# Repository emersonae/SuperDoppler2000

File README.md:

# SuperDoppler2000
BT Send Data H & T

Main loop sends Temperature and Humidity Data from AHT sensor (old sensor no pressure data)

Hm10 Bluetooth: Connect RX to PA9 and TX to PA10 

AHT20: Connect SCL to PB6 and SDA to PB7

If you want to change the message sent, or frequency make changes in the main while loop of "main.c" (core-->src-->main.c)

Rough outline of how to connect HM10 to raspberry pi here: https://docs.google.com/document/d/1dRe9r46AMOh3whqpXwOjyoZfKZXxDHSTZSgcjSjQhZo/edit?usp=sharing

using this tutorial : https://www.youtube.com/watch?v=VRqDqq9hc24

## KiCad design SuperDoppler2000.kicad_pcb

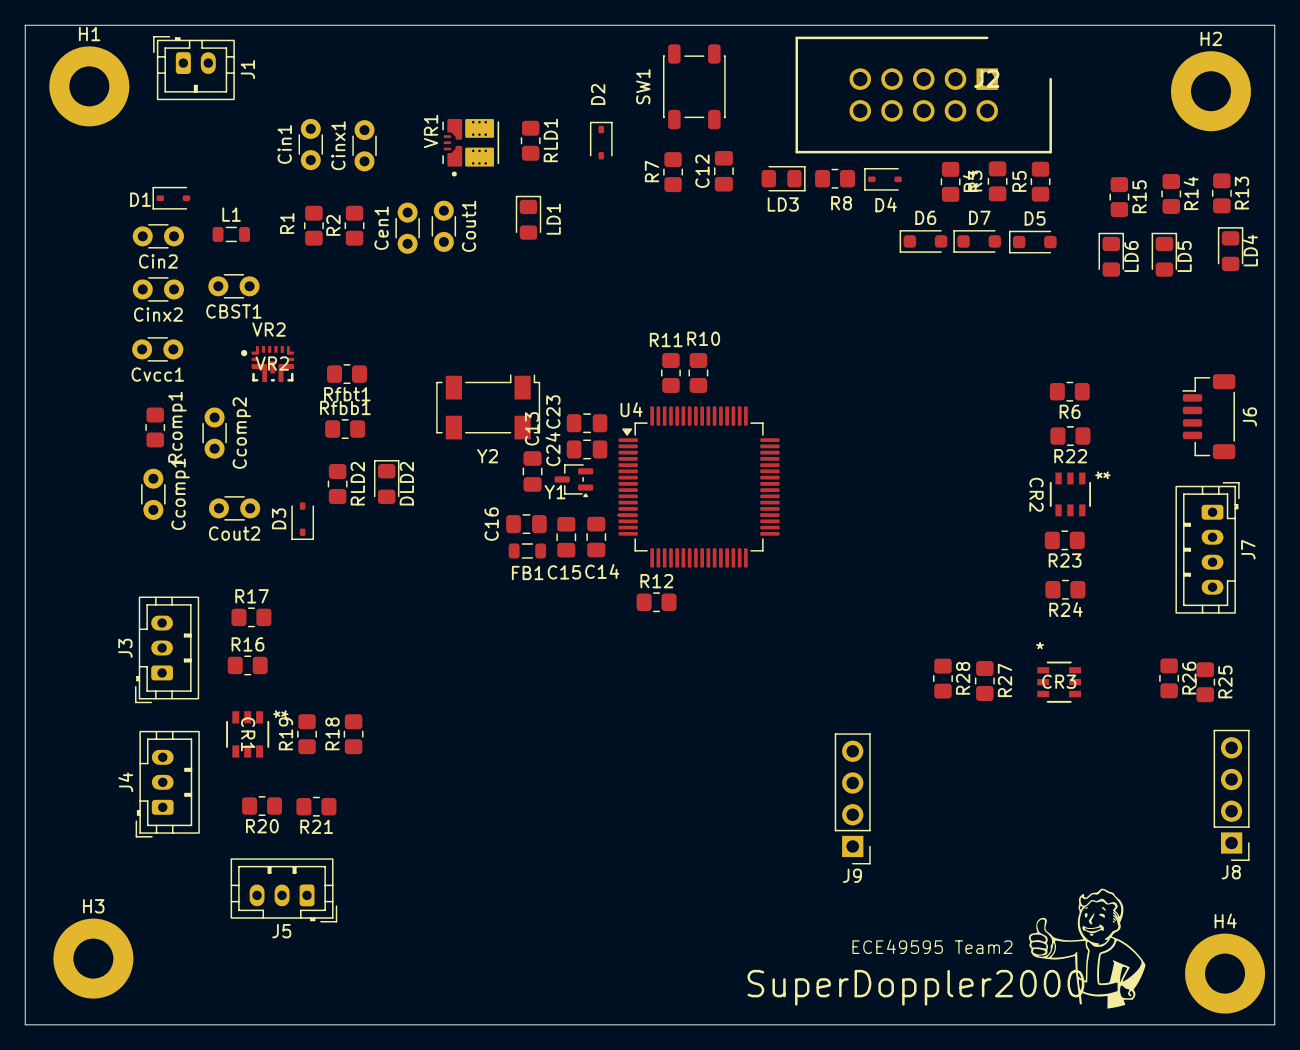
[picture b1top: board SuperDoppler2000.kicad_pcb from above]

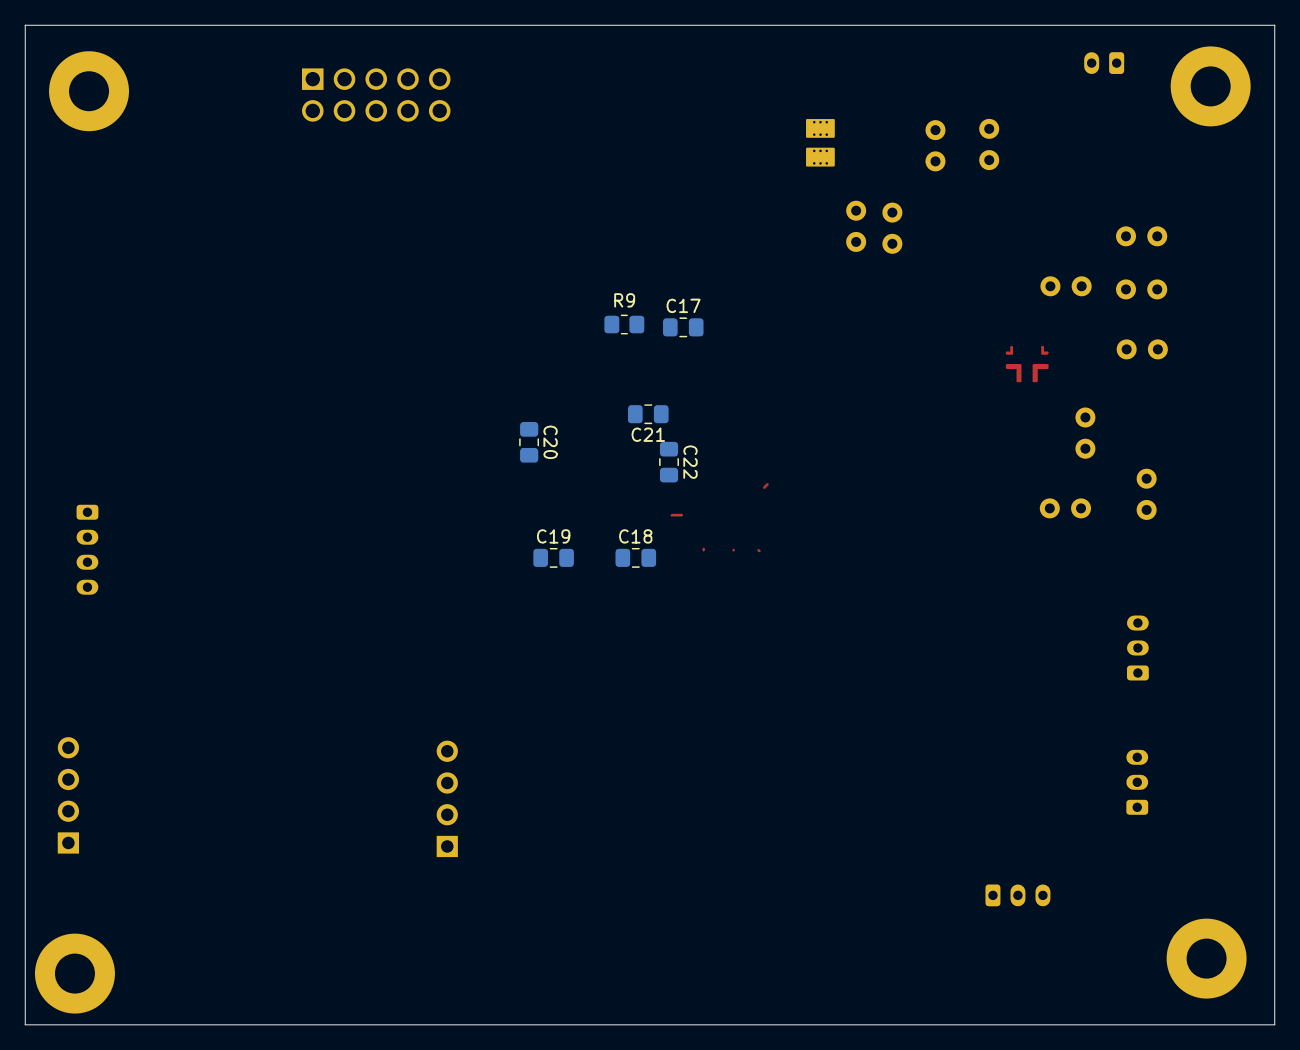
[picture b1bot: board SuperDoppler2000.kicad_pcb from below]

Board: 2 copper layers, 100.0 x 80.0 mm, 94 parts (7 on the bottom side), 58 nets.

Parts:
C12, C13: 0.1u; C_0805_2012Metric_Pad1.18x1.45mm_HandSolder
C14: 10n; C_0805_2012Metric_Pad1.18x1.45mm_HandSolder
C15, C16: 1u; C_0805_2012Metric_Pad1.18x1.45mm_HandSolder
C17: 4.7u; C_0805_2012Metric_Pad1.18x1.45mm_HandSolder
C18, C19, C20, C21, C22: 100n; C_0805_2012Metric_Pad1.18x1.45mm_HandSolder
C23, C24: 8pF; C_0805_2012Metric_Pad1.18x1.45mm_HandSolder
CBST1: 100nF; C_Disc_D3.0mm_W1.6mm_P2.50mm
CR1: DALC208SC6; SOT23-6L_STM
CR2, CR3: D1213A-04TS-7; TSOT26_DIO
Ccomp1: 39nF; C_Disc_D3.0mm_W1.6mm_P2.50mm
Ccomp2: 68nF; C_Disc_D3.0mm_W1.6mm_P2.50mm
Cen1: 10nF; C_Disc_D3.0mm_W1.6mm_P2.50mm
Cin1, Cin2: 10uF; C_Disc_D3.0mm_W1.6mm_P2.50mm
Cinx1, Cinx2: 100nF; C_Disc_D3.0mm_W1.6mm_P2.50mm
Cout1: 22uF; C_Disc_D3.0mm_W1.6mm_P2.50mm
Cout2: 47uF; C_Disc_D3.0mm_W1.6mm_P2.50mm
Cvcc1: 2.2uF; C_Disc_D3.0mm_W1.6mm_P2.50mm
D1: ESD9B5.0ST5G; D_SOD-323
D2, D3, D4: BAT60A; D_SOD-323
D5, D6, D7: GSESLC3V3D323S-2B; D_SOD-323_HandSoldering
DLD2: LED_Red; LED_0805_2012Metric_Pad1.15x1.40mm_HandSolder
FB1: FerriteBead; L_0805_2012Metric
H1, H2, H3, H4: MountingHole_Pad; MountingHole_3.2mm_M3_Pad
J1: JST PH; JST_PH_B2B-PH-K_1x02_P2.00mm_Vertical
J2: IDC 2x05 2.54mm; SHDR10W66P254_2X5_2019X914X986P
J3, J4, J5: JST PH; JST_PH_B3B-PH-K_1x03_P2.00mm_Vertical
J6: JST SH; JST_SH_BM04B-SRSS-TB_1x04-1MP_P1.00mm_Vertical
J7: JST PH; JST_PH_B4B-PH-K_1x04_P2.00mm_Vertical
J8, J9: TBD; PinHeader_1x04_P2.54mm_Vertical
L1: 4.7uH; L_0805_2012Metric
LD1, LD3: LED_Red; LED_0805_2012Metric_Pad1.15x1.40mm_HandSolder
LD4: LED_Green; LED_0805_2012Metric_Pad1.15x1.40mm_HandSolder
LD5: LED_Yellow; LED_0805_2012Metric_Pad1.15x1.40mm_HandSolder
LD6: LED_Blue; LED_0805_2012Metric_Pad1.15x1.40mm_HandSolder
R1: 14.7k; R_0805_2012Metric_Pad1.20x1.40mm_HandSolder
R2: 10kOhms; R_0805_2012Metric_Pad1.20x1.40mm_HandSolder
R3, R4, R5, R6, R22, R23, R24, R25, R26, R27, R28: 220; R_0805_2012Metric_Pad1.20x1.40mm_HandSolder
R7: 100K; R_0805_2012Metric_Pad1.20x1.40mm_HandSolder
R8: 150; R_0805_2012Metric_Pad1.20x1.40mm_HandSolder
R9: 100k; R_0805_2012Metric_Pad1.20x1.40mm_HandSolder
R10, R11: 4.7k; R_0805_2012Metric_Pad1.20x1.40mm_HandSolder
R12, R15: 0; R_0805_2012Metric_Pad1.20x1.40mm_HandSolder
R13: 100; R_0805_2012Metric_Pad1.20x1.40mm_HandSolder
R14: 65; R_0805_2012Metric_Pad1.20x1.40mm_HandSolder
R16, R18, R20: 10k; R_0805_2012Metric_Pad1.20x1.40mm_HandSolder
R17, R19, R21: 14k; R_0805_2012Metric_Pad1.20x1.40mm_HandSolder
RLD1: 150; R_0805_2012Metric_Pad1.20x1.40mm_HandSolder
RLD2: 500; R_0805_2012Metric_Pad1.20x1.40mm_HandSolder
Rcomp1: 26.7kOhms; R_0805_2012Metric_Pad1.20x1.40mm_HandSolder
Rfbb1: 48.7kOhms; R_0805_2012Metric_Pad1.20x1.40mm_HandSolder
Rfbt1: 931kOhms; R_0805_2012Metric_Pad1.20x1.40mm_HandSolder
SW1: SW_Push; SW_SPST_PTS647_Sx50
U4: STM32L152RETx; LQFP-64_10x10mm_P0.5mm
VR1: TPSM863253RDXR; VREG_TPSM863253RDXR
VR2: TPS61288RQQR; RQQ0011A-MFG
Y1: MAX7375AXR805; SOT-323_SC-70
Y2: ABS25-32.768KHZ-6-T; Crystal_SMD_Abracon_ABS25-4Pin_8.0x3.8mm

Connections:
+3.3V: C13.2, C17.1, C18.1, C19.1, C20.1, C21.1, C22.1, D2.1 (K), J6.2, J7.2, J8.1, J9.1, R7.1, R10.2, R11.2, U4.1 (VLCD), U4.19 (VDD), U4.32 (VDD), U4.48 (VDD), U4.64 (VDD), Y1.1 (V+)
+3.3VA: C14.1, C15.1, C16.1, FB1.1, FB1.2, U4.13 (VDDA)
+4.5_or_+5: Cin1.1, Cin2.1, Cinx1.1, Cinx2.1, D1.2 (A2), D4.1 (K), J1.2, L1.1, R1.1, R8.2, VR1.1 (VIN), VR2.6 (EN), VR2.7 (VIN)
+12V: D3.1 (K), J3.1, J4.1, J5.1
/STM32-L152RE/NRST: C12.1, D5.2 (A2), R5.1, R7.2, SW1.2, U4.7 (NRST)
/STM32-L152RE/OSC32_IN: C23.2, U4.3 (PC14), Y2.1 (CRYSTAL_1), Y2.2 (NC_1)
/STM32-L152RE/OSC32_OUT: C24.1, U4.4 (PC15), Y2.3 (NC_2), Y2.4 (CRYSTAL_2)
/STM32-L152RE/PB12: R13.1, U4.33 (PB12)
/STM32-L152RE/PB13: R15.1, U4.34 (PB13)
/STM32-L152RE/PB14: R14.1, U4.35 (PB14)
/STM32-L152RE/RCC_OSC_IN: U4.5 (PH0), Y1.2 (CLOCK)
/STM32-L152RE/SWCLK: D7.2 (A2), R4.2, U4.49 (PA14)
/STM32-L152RE/SWDIO: D6.2 (A2), R3.2, U4.46 (PA13)
ADC_IN6: R16.2, R17.1, U4.21 (PA5)
ADC_IN7: R18.2, R19.1, U4.22 (PA6)
ADC_IN14: R20.2, R21.1, U4.24 (PC4)
GND: C12.2, C13.1, C14.2, C15.2, C16.2, C17.2, C18.2, C19.2, C20.2, C21.2, C22.2, C23.1, C24.2, CR1.5 (REF1), CR2.2, CR3.2, Ccomp1.2, Ccomp2.2, Cen1.2, Cin1.2, Cin2.2, Cinx1.2, Cinx2.2, Cout1.2, Cout2.2, Cvcc1.2, D1.1 (A1), D5.1 (A1), D6.1 (A1), D7.1 (A1), DLD2.1 (K), J1.1, J2.3, J2.4, J3.3, J4.3, J5.3, J6.1, J7.1, J8.2, J9.2, LD1.1 (K), LD3.1 (K), LD4.1 (K), LD5.1 (K), LD6.1 (K), R2.2, R9.1, R12.1, R16.1, R18.1, R20.1, Rfbb1.2, SW1.1, U4.18 (VSS), U4.31 (VSS), U4.47 (VSS), U4.63 (VSS), VR1.4 (PGND), VR2.3 (PGND), VR2.10 (AGND), Y1.3 (GND)
GNDA: R12.2, U4.12 (VSSA)
I2C1SCL: R10.1, U4.58 (PB6)
I2C1_SCL: CR2.6, R22.1
I2C1_SDA: CR2.1, R6.1, R11.1, U4.59 (PB7)
I2C2_SCL: CR2.4, R24.1, U4.29 (PB10)
I2C2_SDA: CR2.3, R23.1, U4.30 (PB11)
unnamed: CBST1.1, L1.2, VR2.4 (SW), VR2.9 (SW)
unnamed: CR1.1 (I/O1), J3.2, R17.2
unnamed: CR1.4 (I/O3), J5.2, R21.2
unnamed: CR1.6 (I/O4), J4.2, R19.2
unnamed: Ccomp1.1, Rcomp1.2
unnamed: Cout1.1, D2.2 (A), RLD1.1, VR1.3 (VOUT), VR1.7 (FB)
unnamed: Cout2.1, D3.2 (A), RLD2.1, Rfbt1.1, VR2.5 (VOUT)
unnamed: D4.2 (A), J2.10
unnamed: DLD2.2 (A), RLD2.2
unnamed: J2.1, R5.2
unnamed: J2.2, R3.1
unnamed: J2.6, R4.1
unnamed: J6.3, R6.2
unnamed: J6.4, R22.2
unnamed: J7.3, R23.2
unnamed: J7.4, R24.2
unnamed: J8.3, R25.1
unnamed: J8.4, R26.1
unnamed: J9.3, R27.2
unnamed: J9.4, R28.2
unnamed: LD1.2 (A), RLD1.2
unnamed: LD3.2 (A), R8.1
unnamed: LD4.2 (A), R13.2
unnamed: LD5.2 (A), R14.2
unnamed: LD6.2 (A), R15.2
unnamed: R9.2, U4.60 (BOOT0)
unnamed: Cen1.1, R1.2, R2.1, VR1.6 (EN)
unnamed: CBST1.2, VR2.8 (BST)
unnamed: Ccomp2.1, Rcomp1.1, VR2.2 (COMP)
unnamed: Rfbb1.1, Rfbt1.2, VR2.1 (FB)
unnamed: Cvcc1.1, VR2.11 (VCC)
USART1_RX: CR3.1, R26.2, U4.43 (PA10)
USART1_TX: CR3.6, R25.2, U4.42 (PA9)
USART3_RX: CR3.3, R28.1, U4.52 (PC11)
USART3_TX: CR3.4, R27.1, U4.51 (PC10)

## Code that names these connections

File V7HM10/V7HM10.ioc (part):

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Mcu.Name=STM32L152RETx
Mcu.Package=LQFP64
Mcu.UserName=STM32L152RETx
PA10.Mode=Asynchronous
PA10.Signal=USART1_RX
PA13.GPIOParameters=GPIO_Label
PA13.GPIO_Label=TMS
PA13.Mode=Serial_Wire
PA13.Signal=SYS_JTMS-SWDIO
PA14.GPIOParameters=GPIO_Label
PA14.GPIO_Label=TCK
PA14.Mode=Serial_Wire
PA14.Signal=SYS_JTCK-SWCLK
PA6.Signal=S_TIM3_CH1
PA7.Mode=IN7
PA7.Signal=ADC_IN7
PA9.Mode=Asynchronous
PA9.Signal=USART1_TX
PB0.Signal=S_TIM3_CH3
PB1.Signal=S_TIM3_CH4
PB10.Mode=I2C
PB10.Signal=I2C2_SCL
PB11.Mode=I2C
PB11.Signal=I2C2_SDA
PB3.GPIOParameters=GPIO_Label
PB3.GPIO_Label=SWO
PB3.Signal=SYS_JTDO-TRACESWO
PB5.Signal=S_TIM3_CH2
PC14-OSC32_IN.Mode=LSE-External-Oscillator
PC14-OSC32_IN.Signal=RCC_OSC32_IN
PC15-OSC32_OUT.Mode=LSE-External-Oscillator
PC15-OSC32_OUT.Signal=RCC_OSC32_OUT
PC4.Mode=IN14
PC4.Signal=ADC_IN14
PC7.Signal=GPIO_Output
PC8.Signal=GPIO_Output
PC9.Signal=GPIO_Output
PH0-OSC_IN.Mode=HSE-External-Oscillator
PH0-OSC_IN.Signal=RCC_OSC_IN
PH1-OSC_OUT.Mode=HSE-External-Oscillator
PH1-OSC_OUT.Signal=RCC_OSC_OUT
RCC.HSE_VALUE=8000000
RCC.SYSCLKFreq_VALUE=32000000
RCC.SYSCLKSource=RCC_SYSCLKSOURCE_PLLCLK
board=NUCLEO-L152RE
boardIOC=true

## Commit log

2026-01-21 comments
2026-01-21 basic send, recieve loop
2026-01-21 send/recieve loop
2026-01-22 Send/Recieve circular DMA
2026-01-22 initial temp & humidity with timer
2026-01-22 timer interrupt broken (check clock settings)
2026-02-04 oscillator + header + connectors
2026-02-04 analog connection
2026-02-04 add buck
2026-02-05 footprints & schem
2026-02-09 updated schematic
2026-02-12 Add files via upload
    starting layout
2026-02-16 board layout
2026-02-25 v8 matches webench
2026-02-26 V10 has correct footprints
2026-03-10 V15 w/fixes
2026-03-20 BT send H&T
2026-03-20 start interupt timer(IT)
2026-04-05 Start on sleep mode
2026-04-09 BME280 code
2026-04-10 fix build errors
2026-04-10 half working
2026-04-21 functions but data not good
2026-04-21 new branch
2026-04-21 start analog
2026-04-21 BT working, used 16MHZ internal CLK
2026-04-21 fix clock
2026-04-21 initail setup
2026-04-22 minor fixes
2026-04-22 immediate error but compiles. We should set up wires to use I2C2
2026-04-22 double check wiring for I2C2, PB10, PB11
